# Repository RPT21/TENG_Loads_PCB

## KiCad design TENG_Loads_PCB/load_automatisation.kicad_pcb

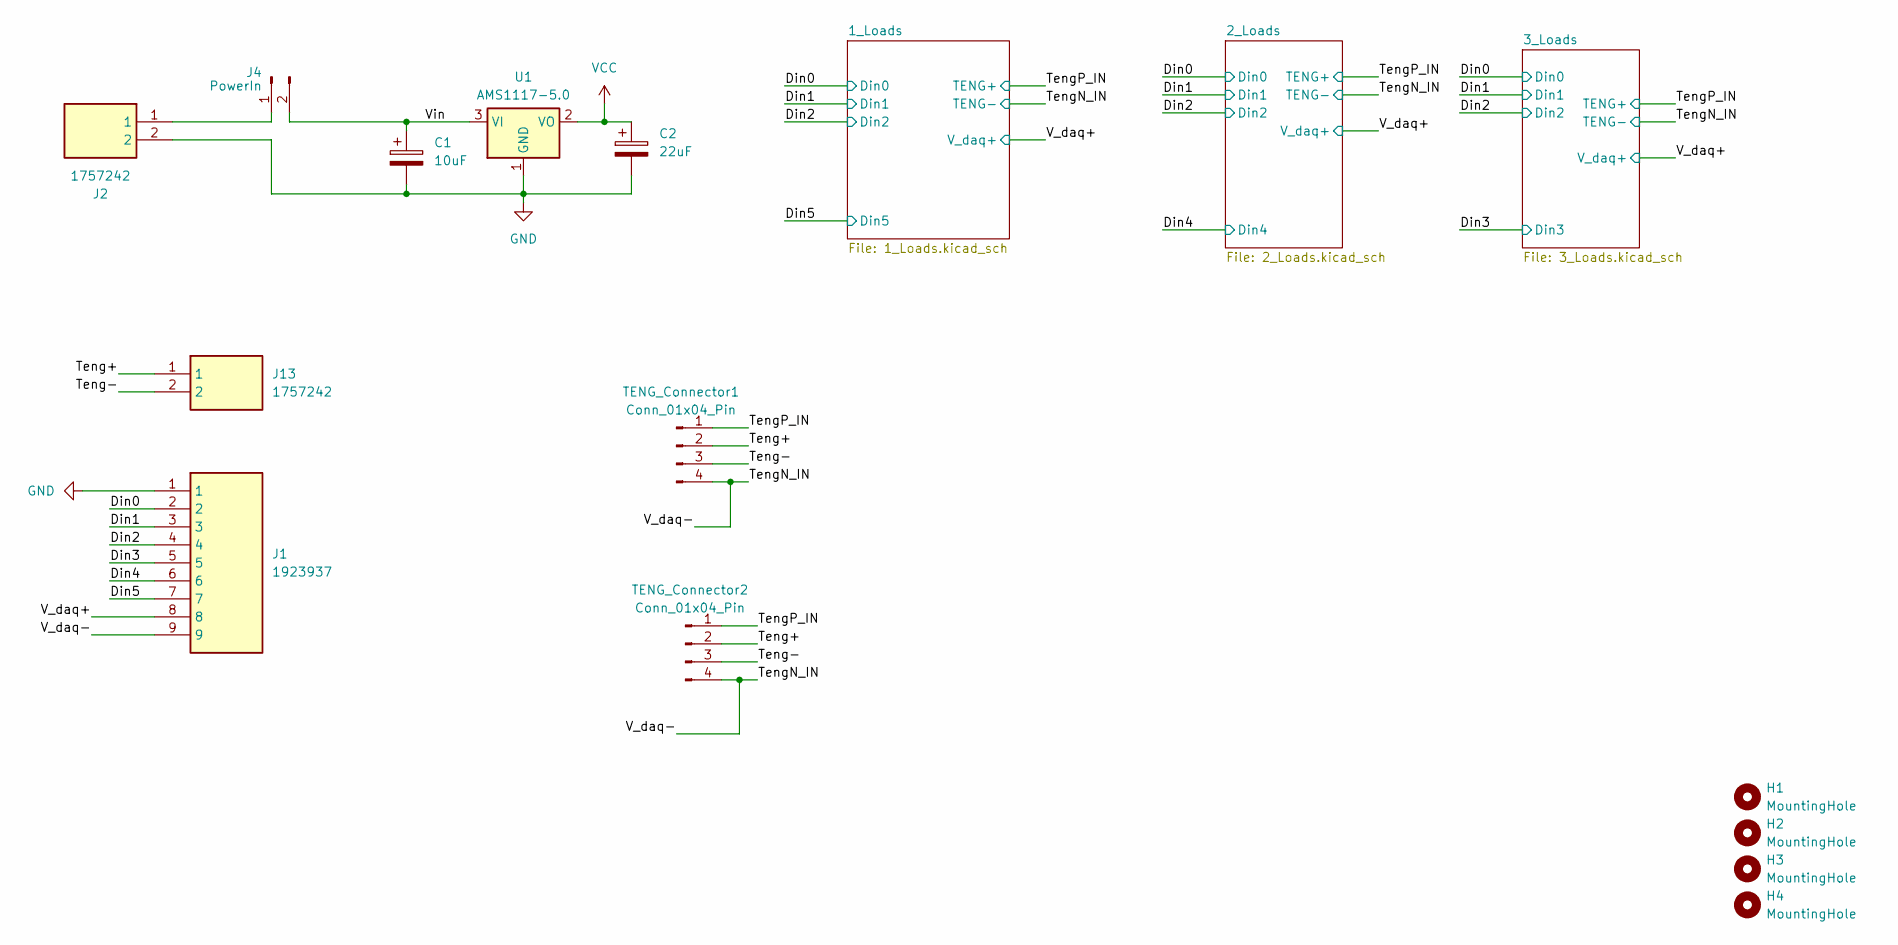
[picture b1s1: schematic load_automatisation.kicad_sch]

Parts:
C1: 10uF; CP_Radial_D8.0mm_P3.80mm
C2: 22uF; CP_Radial_D8.0mm_P3.80mm
H1, H2, H3, H4: MountingHole; MountingHole_5.3mm_M5
J1: 1923937; Mouser Part Number 651-1923937
J2, J13: 1757242; Manufacturer_Part_Number 1757242; Mouser Part Number 651-1757242
J4: PowerIn; PinHeader_1x02_P2.54mm_Vertical
TENG_Connector1, TENG_Connector2: Conn_01x04_Pin; PinHeader_1x04_P2.54mm_Vertical
U1: AMS1117-5.0; SOT-223-3_TabPin2

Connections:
/Din0: J1.2; also elsewhere on the board
/Din1: J1.3; also elsewhere on the board
/Din2: J1.4; also elsewhere on the board
/Din3: J1.5; also elsewhere on the board
/Din4: J1.6; also elsewhere on the board
/Din5: J1.7; also elsewhere on the board
/Teng+: J13.1, TENG_Connector1.2, TENG_Connector2.2
/Teng-: J13.2, TENG_Connector1.3, TENG_Connector2.3
/TengN_IN: J1.9, TENG_Connector1.4, TENG_Connector2.4; also elsewhere on the board
/TengP_IN: TENG_Connector1.1, TENG_Connector2.1; also elsewhere on the board
/V_daq+: J1.8; also elsewhere on the board
/Vin: C1.1, J4.2, U1.3 (VI)
GND: C1.2, C2.2, J1.1, J2.2, U1.1 (GND); also elsewhere on the board
unnamed: J2.1, J4.1
VCC: C2.1, U1.2 (VO); also elsewhere on the board

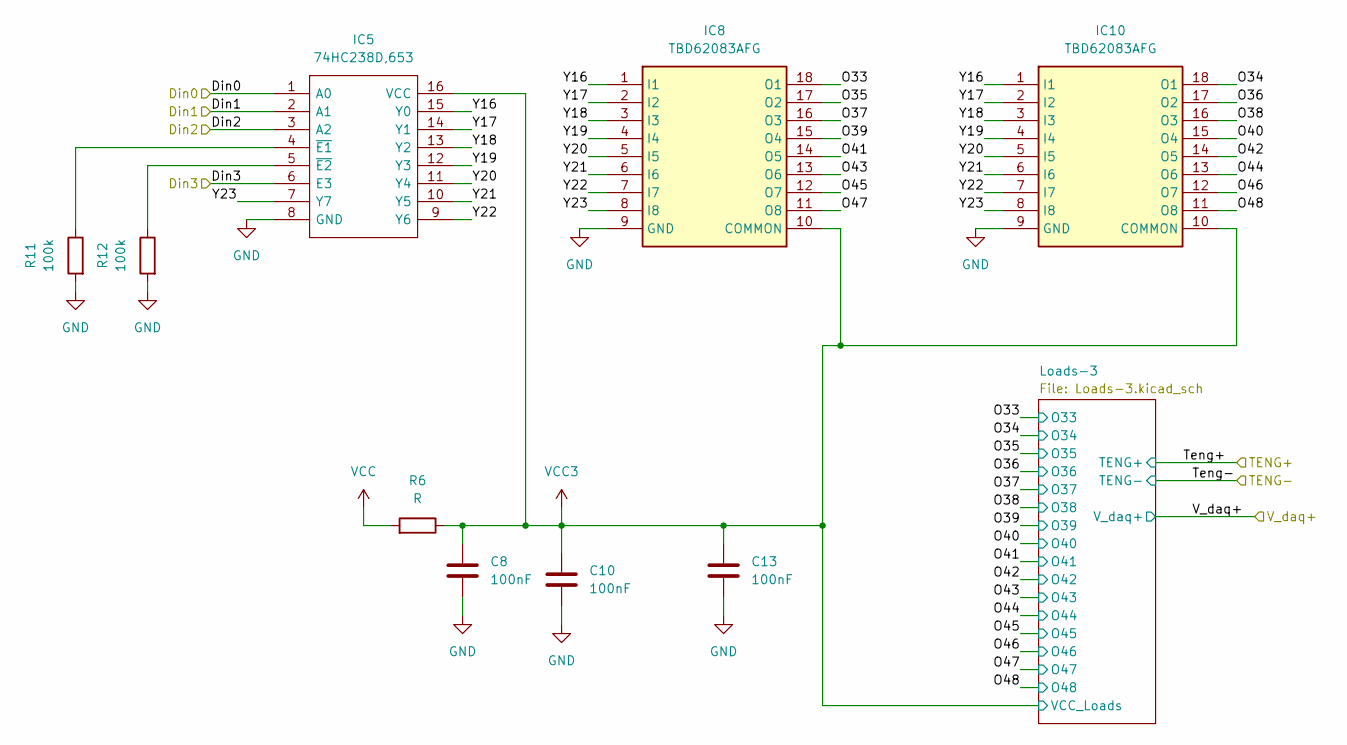
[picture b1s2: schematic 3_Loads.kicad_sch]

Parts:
C8, C10, C13: 100nF; C_0805_2012Metric
IC5: 74HC238D,653; 74HC238D653; Manufacturer_Part_Number 74HC238D,653; Mouser Part Number 771-74HC238D-T
IC8, IC10: TBD62083AFG; SOIC127P1030X245-18N; Manufacturer_Part_Number TD62083AFGNEL; Mouser Part Number N/A
R6: R; R_0805_2012Metric
R11, R12: 100k; R_0805_2012Metric

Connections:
/3_Loads/O33: IC8.18 (O1); also elsewhere on the board
/3_Loads/O34: IC10.18 (O1); also elsewhere on the board
/3_Loads/O35: IC8.17 (O2); also elsewhere on the board
/3_Loads/O36: IC10.17 (O2); also elsewhere on the board
/3_Loads/O37: IC8.16 (O3); also elsewhere on the board
/3_Loads/O38: IC10.16 (O3); also elsewhere on the board
/3_Loads/O39: IC8.15 (O4); also elsewhere on the board
/3_Loads/O40: IC10.15 (O4); also elsewhere on the board
/3_Loads/O41: IC8.14 (O5); also elsewhere on the board
/3_Loads/O42: IC10.14 (O5); also elsewhere on the board
/3_Loads/O43: IC8.13 (O6); also elsewhere on the board
/3_Loads/O44: IC10.13 (O6); also elsewhere on the board
/3_Loads/O45: IC8.12 (O7); also elsewhere on the board
/3_Loads/O46: IC10.12 (O7); also elsewhere on the board
/3_Loads/O47: IC8.11 (O8); also elsewhere on the board
/3_Loads/O48: IC10.11 (O8); also elsewhere on the board
/3_Loads/Y16: IC5.15 (Y0), IC8.1 (I1), IC10.1 (I1)
/3_Loads/Y17: IC5.14 (Y1), IC8.2 (I2), IC10.2 (I2)
/3_Loads/Y18: IC5.13 (Y2), IC8.3 (I3), IC10.3 (I3)
/3_Loads/Y19: IC5.12 (Y3), IC8.4 (I4), IC10.4 (I4)
/3_Loads/Y20: IC5.11 (Y4), IC8.5 (I5), IC10.5 (I5)
/3_Loads/Y21: IC5.10 (Y5), IC8.6 (I6), IC10.6 (I6)
/3_Loads/Y22: IC5.9 (Y6), IC8.7 (I7), IC10.7 (I7)
/3_Loads/Y23: IC5.7 (Y7), IC8.8 (I8), IC10.8 (I8)
/Din0: IC5.1 (A0); also elsewhere on the board
/Din1: IC5.2 (A1); also elsewhere on the board
/Din2: IC5.3 (A2); also elsewhere on the board
/Din3: IC5.6 (E3); also elsewhere on the board
GND: C8.2, C10.2, C13.2, IC5.8 (GND), IC8.9 (GND), IC10.9 (GND), R11.2, R12.2; also elsewhere on the board
unnamed: IC5.4 (~E1), R11.1
unnamed: IC5.5 (~E2), R12.1
VCC: R6.2; also elsewhere on the board
VCC3: C8.1, C10.1, C13.1, IC5.16 (VCC), IC8.10 (COMMON), IC10.10 (COMMON), R6.1; also elsewhere on the board

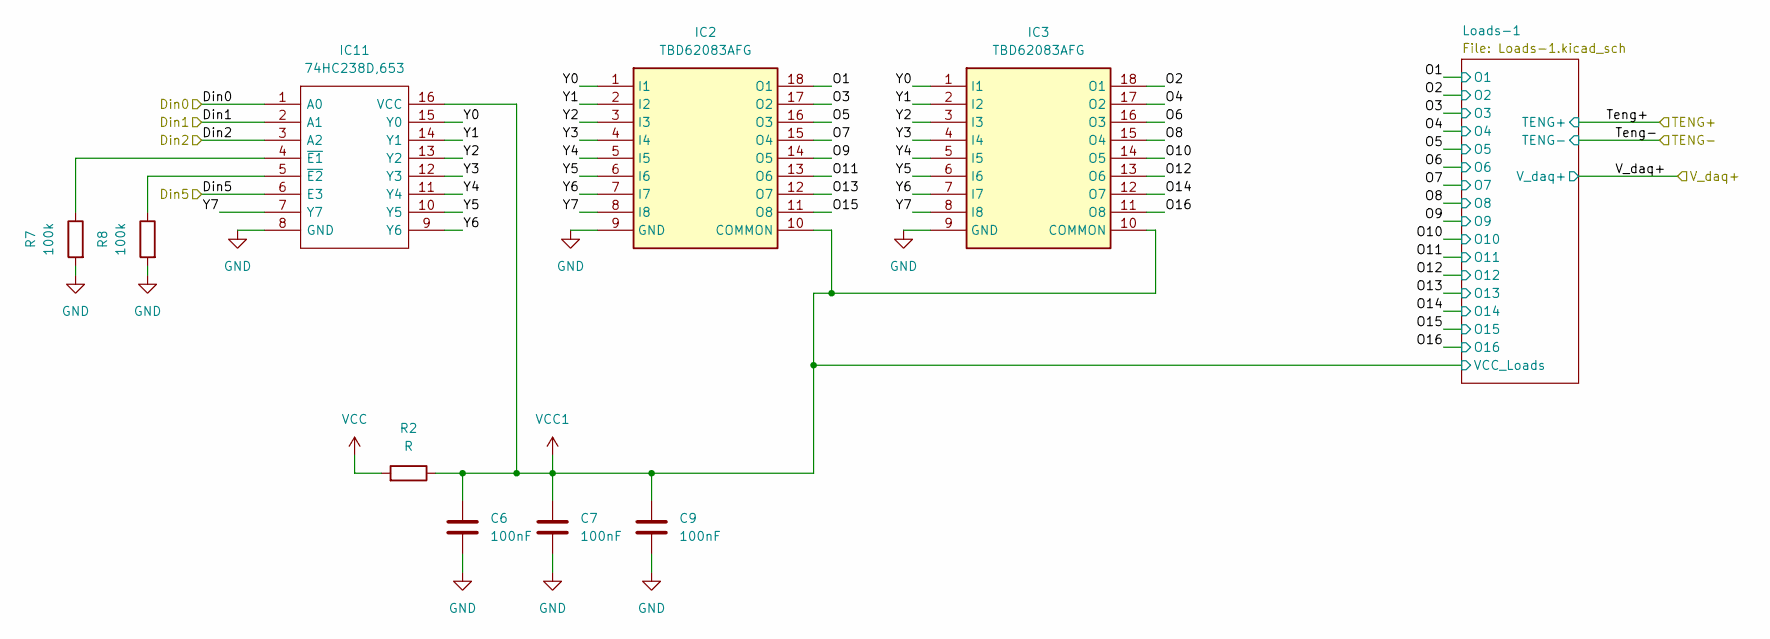
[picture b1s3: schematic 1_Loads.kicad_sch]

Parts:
C6, C7, C9: 100nF; C_0805_2012Metric
IC2, IC3: TBD62083AFG; SOIC127P1030X245-18N; Manufacturer_Part_Number TD62083AFGNEL; Mouser Part Number N/A
IC11: 74HC238D,653; 74HC238D653; Manufacturer_Part_Number 74HC238D,653; Mouser Part Number 771-74HC238D-T
R2: R; R_0805_2012Metric
R7, R8: 100k; R_0805_2012Metric

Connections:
/1_Loads/O1: IC2.18 (O1); also elsewhere on the board
/1_Loads/O2: IC3.18 (O1); also elsewhere on the board
/1_Loads/O3: IC2.17 (O2); also elsewhere on the board
/1_Loads/O4: IC3.17 (O2); also elsewhere on the board
/1_Loads/O5: IC2.16 (O3); also elsewhere on the board
/1_Loads/O6: IC3.16 (O3); also elsewhere on the board
/1_Loads/O7: IC2.15 (O4); also elsewhere on the board
/1_Loads/O8: IC3.15 (O4); also elsewhere on the board
/1_Loads/O9: IC2.14 (O5); also elsewhere on the board
/1_Loads/O10: IC3.14 (O5); also elsewhere on the board
/1_Loads/O11: IC2.13 (O6); also elsewhere on the board
/1_Loads/O12: IC3.13 (O6); also elsewhere on the board
/1_Loads/O13: IC2.12 (O7); also elsewhere on the board
/1_Loads/O14: IC3.12 (O7); also elsewhere on the board
/1_Loads/O15: IC2.11 (O8); also elsewhere on the board
/1_Loads/O16: IC3.11 (O8); also elsewhere on the board
/1_Loads/Y0: IC2.1 (I1), IC3.1 (I1), IC11.15 (Y0)
/1_Loads/Y1: IC2.2 (I2), IC3.2 (I2), IC11.14 (Y1)
/1_Loads/Y2: IC2.3 (I3), IC3.3 (I3), IC11.13 (Y2)
/1_Loads/Y3: IC2.4 (I4), IC3.4 (I4), IC11.12 (Y3)
/1_Loads/Y4: IC2.5 (I5), IC3.5 (I5), IC11.11 (Y4)
/1_Loads/Y5: IC2.6 (I6), IC3.6 (I6), IC11.10 (Y5)
/1_Loads/Y6: IC2.7 (I7), IC3.7 (I7), IC11.9 (Y6)
/1_Loads/Y7: IC2.8 (I8), IC3.8 (I8), IC11.7 (Y7)
/Din0: IC11.1 (A0); also elsewhere on the board
/Din1: IC11.2 (A1); also elsewhere on the board
/Din2: IC11.3 (A2); also elsewhere on the board
/Din5: IC11.6 (E3); also elsewhere on the board
GND: C6.2, C7.2, C9.2, IC2.9 (GND), IC3.9 (GND), IC11.8 (GND), R7.2, R8.2; also elsewhere on the board
unnamed: IC11.4 (~E1), R7.1
unnamed: IC11.5 (~E2), R8.1
VCC: R2.2; also elsewhere on the board
VCC1: C6.1, C7.1, C9.1, IC2.10 (COMMON), IC3.10 (COMMON), IC11.16 (VCC), R2.1; also elsewhere on the board

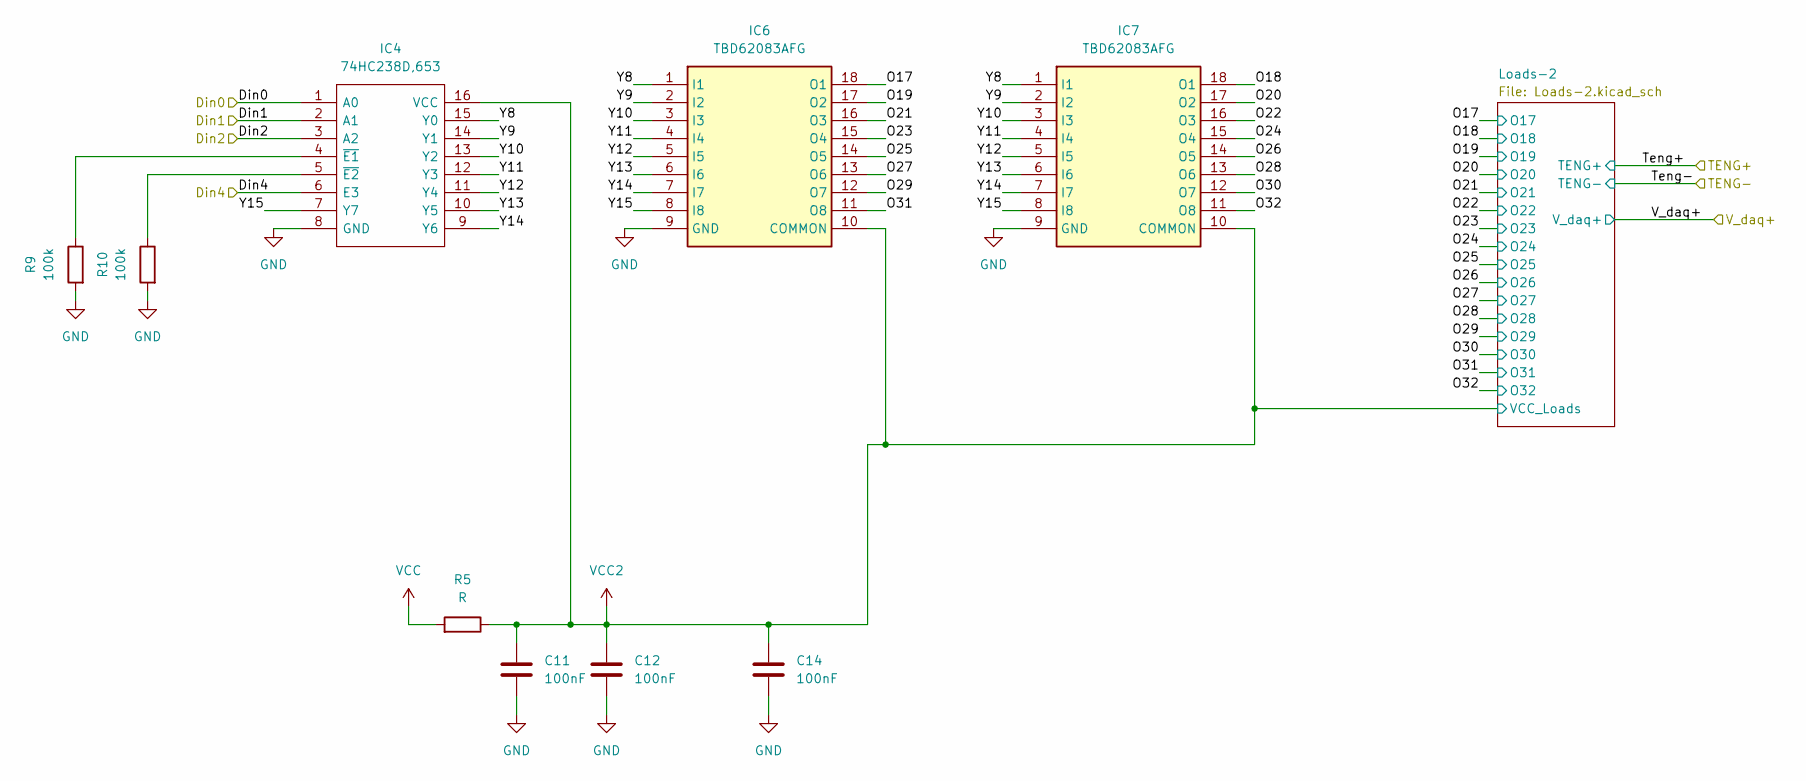
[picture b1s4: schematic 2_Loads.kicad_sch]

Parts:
C11, C12, C14: 100nF; C_0805_2012Metric
IC4: 74HC238D,653; 74HC238D653; Manufacturer_Part_Number 74HC238D,653; Mouser Part Number 771-74HC238D-T
IC6, IC7: TBD62083AFG; SOIC127P1030X245-18N; Manufacturer_Part_Number TD62083AFGNEL; Mouser Part Number N/A
R5: R; R_0805_2012Metric
R9, R10: 100k; R_0805_2012Metric

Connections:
/2_Loads/O17: IC6.18 (O1); also elsewhere on the board
/2_Loads/O18: IC7.18 (O1); also elsewhere on the board
/2_Loads/O19: IC6.17 (O2); also elsewhere on the board
/2_Loads/O20: IC7.17 (O2); also elsewhere on the board
/2_Loads/O21: IC6.16 (O3); also elsewhere on the board
/2_Loads/O22: IC7.16 (O3); also elsewhere on the board
/2_Loads/O23: IC6.15 (O4); also elsewhere on the board
/2_Loads/O24: IC7.15 (O4); also elsewhere on the board
/2_Loads/O25: IC6.14 (O5); also elsewhere on the board
/2_Loads/O26: IC7.14 (O5); also elsewhere on the board
/2_Loads/O27: IC6.13 (O6); also elsewhere on the board
/2_Loads/O28: IC7.13 (O6); also elsewhere on the board
/2_Loads/O29: IC6.12 (O7); also elsewhere on the board
/2_Loads/O30: IC7.12 (O7); also elsewhere on the board
/2_Loads/O31: IC6.11 (O8); also elsewhere on the board
/2_Loads/O32: IC7.11 (O8); also elsewhere on the board
/2_Loads/Y8: IC4.15 (Y0), IC6.1 (I1), IC7.1 (I1)
/2_Loads/Y9: IC4.14 (Y1), IC6.2 (I2), IC7.2 (I2)
/2_Loads/Y10: IC4.13 (Y2), IC6.3 (I3), IC7.3 (I3)
/2_Loads/Y11: IC4.12 (Y3), IC6.4 (I4), IC7.4 (I4)
/2_Loads/Y12: IC4.11 (Y4), IC6.5 (I5), IC7.5 (I5)
/2_Loads/Y13: IC4.10 (Y5), IC6.6 (I6), IC7.6 (I6)
/2_Loads/Y14: IC4.9 (Y6), IC6.7 (I7), IC7.7 (I7)
/2_Loads/Y15: IC4.7 (Y7), IC6.8 (I8), IC7.8 (I8)
/Din0: IC4.1 (A0); also elsewhere on the board
/Din1: IC4.2 (A1); also elsewhere on the board
/Din2: IC4.3 (A2); also elsewhere on the board
/Din4: IC4.6 (E3); also elsewhere on the board
GND: C11.2, C12.2, C14.2, IC4.8 (GND), IC6.9 (GND), IC7.9 (GND), R9.2, R10.2; also elsewhere on the board
unnamed: IC4.4 (~E1), R9.1
unnamed: IC4.5 (~E2), R10.1
VCC: R5.2; also elsewhere on the board
VCC2: C11.1, C12.1, C14.1, IC4.16 (VCC), IC6.10 (COMMON), IC7.10 (COMMON), R5.1; also elsewhere on the board

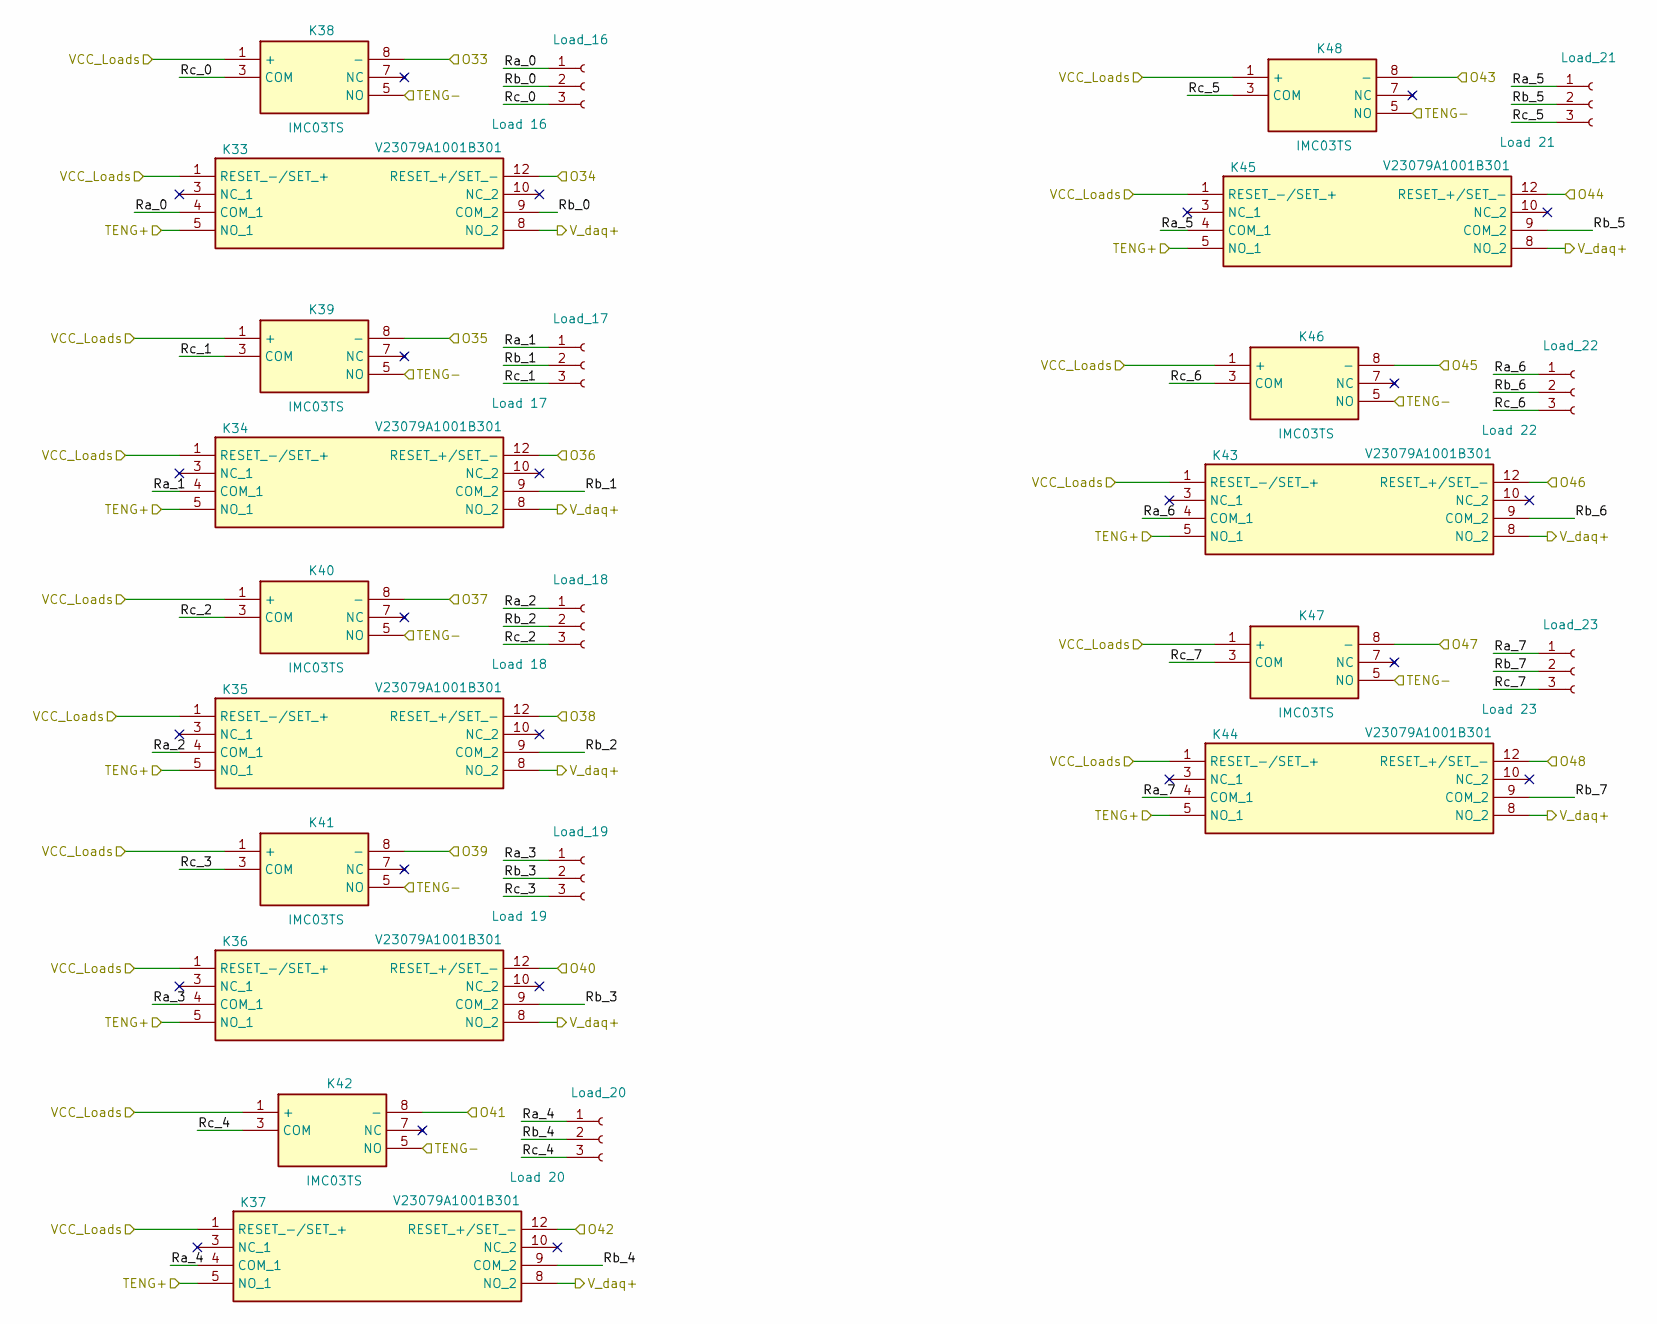
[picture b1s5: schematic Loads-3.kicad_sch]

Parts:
K33, K34, K35, K36, K37, K43, K44, K45: V23079A1001B301; Manufacturer_Part_Number V23079C1103B301; Mouser Part Number 655-V23079C1103B301
K38, K39, K40, K41, K42, K46, K47, K48: IMC03TS; Manufacturer_Part_Number IMC03TS; Mouser Part Number 655-IMC03TS
Load_16: Load 16; PinHeader_1x03_P2.54mm_Vertical
Load_17: Load 17; PinHeader_1x03_P2.54mm_Vertical
Load_18: Load 18; PinHeader_1x03_P2.54mm_Vertical
Load_19: Load 19; PinHeader_1x03_P2.54mm_Vertical
Load_20: Load 20; PinHeader_1x03_P2.54mm_Vertical
Load_21: Load 21; PinHeader_1x03_P2.54mm_Vertical
Load_22: Load 22; PinHeader_1x03_P2.54mm_Vertical
Load_23: Load 23; PinHeader_1x03_P2.54mm_Vertical

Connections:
/3_Loads/Loads-3/Ra_0: K33.4 (COM_1), Load_16.1
/3_Loads/Loads-3/Ra_1: K34.4 (COM_1), Load_17.1
/3_Loads/Loads-3/Ra_2: K35.4 (COM_1), Load_18.1
/3_Loads/Loads-3/Ra_3: K36.4 (COM_1), Load_19.1
/3_Loads/Loads-3/Ra_4: K37.4 (COM_1), Load_20.1
/3_Loads/Loads-3/Ra_5: K45.4 (COM_1), Load_21.1
/3_Loads/Loads-3/Ra_6: K43.4 (COM_1), Load_22.1
/3_Loads/Loads-3/Ra_7: K44.4 (COM_1), Load_23.1
/3_Loads/Loads-3/Rb_0: K33.9 (COM_2), Load_16.2
/3_Loads/Loads-3/Rb_1: K34.9 (COM_2), Load_17.2
/3_Loads/Loads-3/Rb_2: K35.9 (COM_2), Load_18.2
/3_Loads/Loads-3/Rb_3: K36.9 (COM_2), Load_19.2
/3_Loads/Loads-3/Rb_4: K37.9 (COM_2), Load_20.2
/3_Loads/Loads-3/Rb_5: K45.9 (COM_2), Load_21.2
/3_Loads/Loads-3/Rb_6: K43.9 (COM_2), Load_22.2
/3_Loads/Loads-3/Rb_7: K44.9 (COM_2), Load_23.2
/3_Loads/Loads-3/Rc_0: K38.3 (COM), Load_16.3
/3_Loads/Loads-3/Rc_1: K39.3 (COM), Load_17.3
/3_Loads/Loads-3/Rc_2: K40.3 (COM), Load_18.3
/3_Loads/Loads-3/Rc_3: K41.3 (COM), Load_19.3
/3_Loads/Loads-3/Rc_4: K42.3 (COM), Load_20.3
/3_Loads/Loads-3/Rc_5: K48.3 (COM), Load_21.3
/3_Loads/Loads-3/Rc_6: K46.3 (COM), Load_22.3
/3_Loads/Loads-3/Rc_7: K47.3 (COM), Load_23.3
/3_Loads/O33: K38.8 (-); also elsewhere on the board
/3_Loads/O34: K33.12 (RESET_+/SET_-); also elsewhere on the board
/3_Loads/O35: K39.8 (-); also elsewhere on the board
/3_Loads/O36: K34.12 (RESET_+/SET_-); also elsewhere on the board
/3_Loads/O37: K40.8 (-); also elsewhere on the board
/3_Loads/O38: K35.12 (RESET_+/SET_-); also elsewhere on the board
/3_Loads/O39: K41.8 (-); also elsewhere on the board
/3_Loads/O40: K36.12 (RESET_+/SET_-); also elsewhere on the board
/3_Loads/O41: K42.8 (-); also elsewhere on the board
/3_Loads/O42: K37.12 (RESET_+/SET_-); also elsewhere on the board
/3_Loads/O43: K48.8 (-); also elsewhere on the board
/3_Loads/O44: K45.12 (RESET_+/SET_-); also elsewhere on the board
/3_Loads/O45: K46.8 (-); also elsewhere on the board
/3_Loads/O46: K43.12 (RESET_+/SET_-); also elsewhere on the board
/3_Loads/O47: K47.8 (-); also elsewhere on the board
/3_Loads/O48: K44.12 (RESET_+/SET_-); also elsewhere on the board
/TengN_IN: K38.5 (NO), K39.5 (NO), K40.5 (NO), K41.5 (NO), K42.5 (NO), K46.5 (NO), K47.5 (NO), K48.5 (NO); also elsewhere on the board
/TengP_IN: K33.5 (NO_1), K34.5 (NO_1), K35.5 (NO_1), K36.5 (NO_1), K37.5 (NO_1), K43.5 (NO_1), K44.5 (NO_1), K45.5 (NO_1); also elsewhere on the board
/V_daq+: K33.8 (NO_2), K34.8 (NO_2), K35.8 (NO_2), K36.8 (NO_2), K37.8 (NO_2), K43.8 (NO_2), K44.8 (NO_2), K45.8 (NO_2); also elsewhere on the board
VCC3: K33.1 (RESET_-/SET_+), K34.1 (RESET_-/SET_+), K35.1 (RESET_-/SET_+), K36.1 (RESET_-/SET_+), K37.1 (RESET_-/SET_+), K38.1 (+), K39.1 (+), K40.1 (+), K41.1 (+), K42.1 (+), K43.1 (RESET_-/SET_+), K44.1 (RESET_-/SET_+), K45.1 (RESET_-/SET_+), K46.1 (+), K47.1 (+), K48.1 (+); also elsewhere on the board

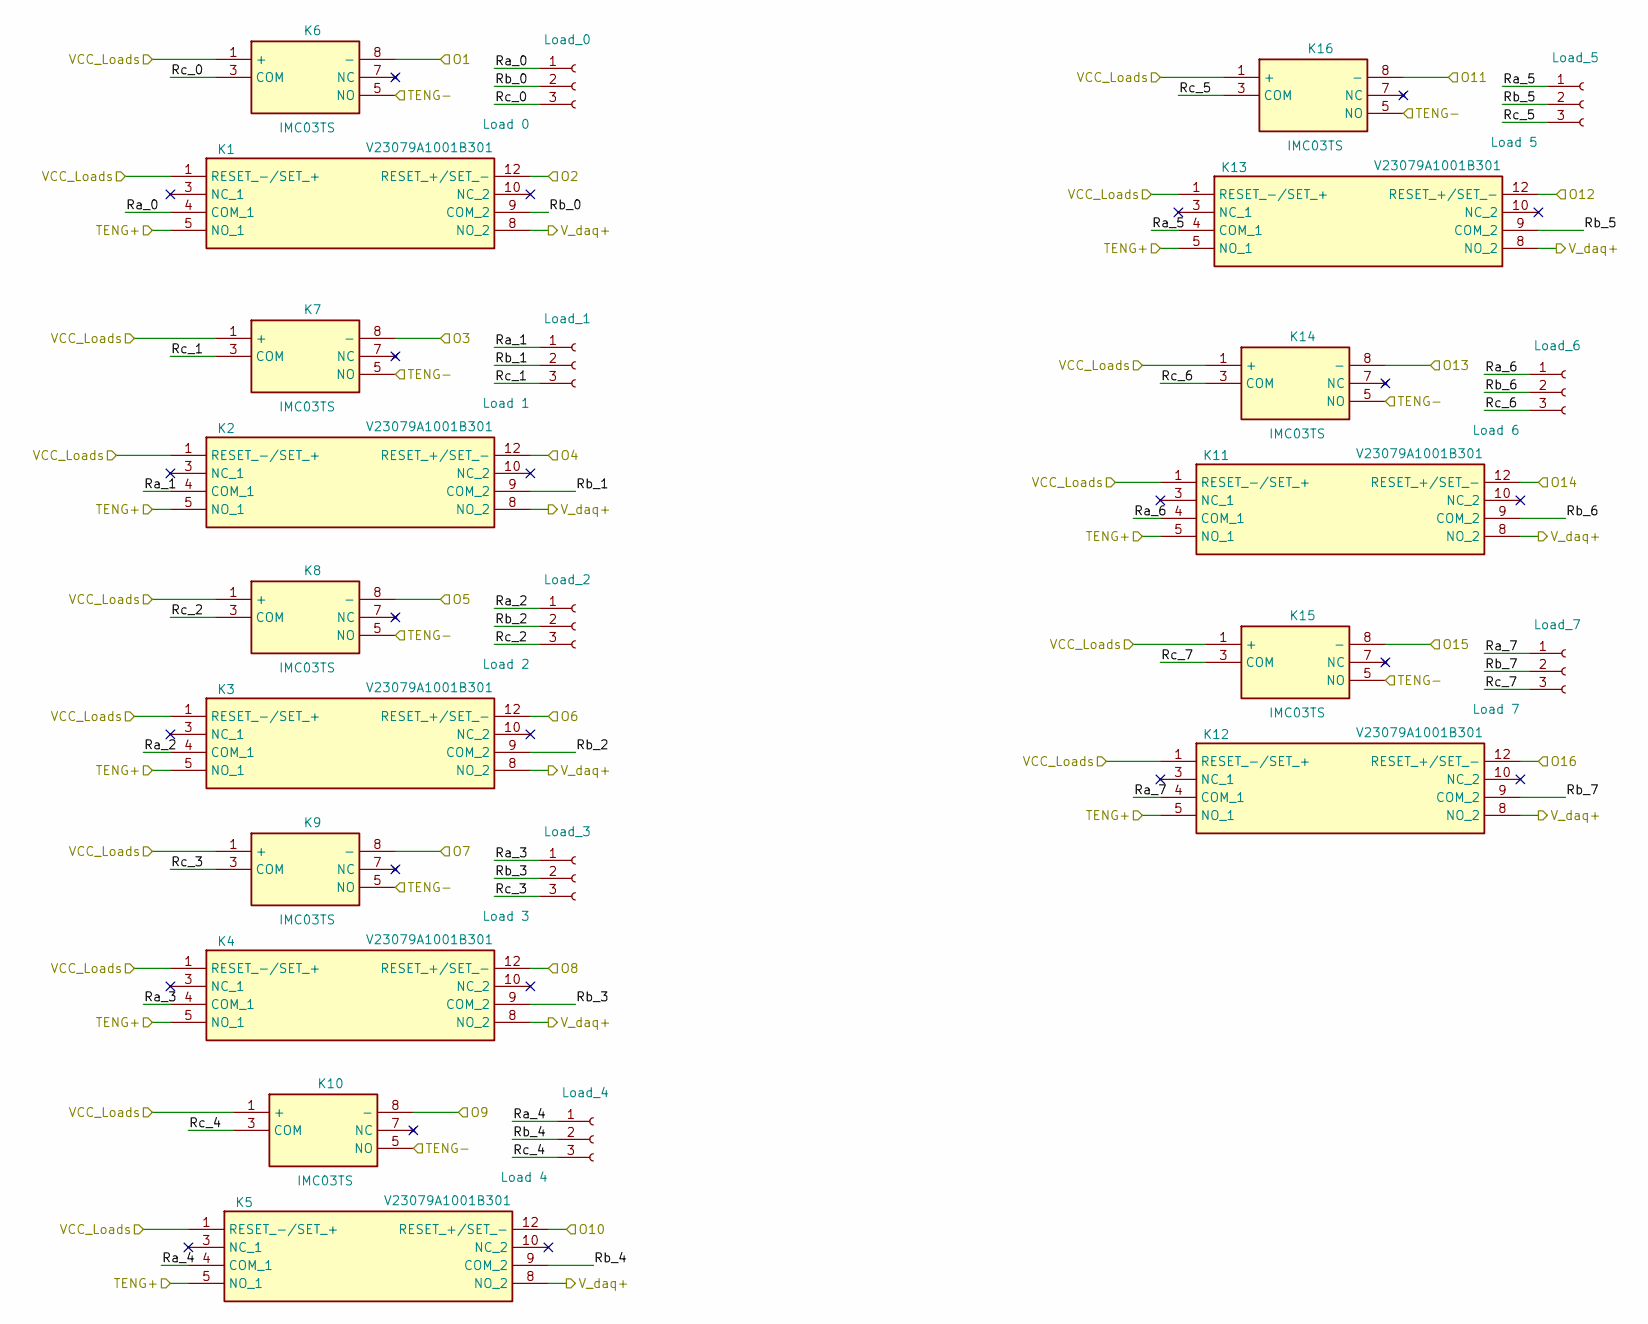
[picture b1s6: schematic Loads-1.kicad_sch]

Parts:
K1, K2, K3, K4, K5, K11, K12, K13: V23079A1001B301; Manufacturer_Part_Number V23079C1103B301; Mouser Part Number 655-V23079C1103B301
K6, K7, K8, K9, K10, K14, K15, K16: IMC03TS; Manufacturer_Part_Number IMC03TS; Mouser Part Number 655-IMC03TS
Load_0: Load 0; PinHeader_1x03_P2.54mm_Vertical
Load_1: Load 1; PinHeader_1x03_P2.54mm_Vertical
Load_2: Load 2; PinHeader_1x03_P2.54mm_Vertical
Load_3: Load 3; PinHeader_1x03_P2.54mm_Vertical
Load_4: Load 4; PinHeader_1x03_P2.54mm_Vertical
Load_5: Load 5; PinHeader_1x03_P2.54mm_Vertical
Load_6: Load 6; PinHeader_1x03_P2.54mm_Vertical
Load_7: Load 7; PinHeader_1x03_P2.54mm_Vertical

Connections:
/1_Loads/Loads-1/Ra_0: K1.4 (COM_1), Load_0.1
/1_Loads/Loads-1/Ra_1: K2.4 (COM_1), Load_1.1
/1_Loads/Loads-1/Ra_2: K3.4 (COM_1), Load_2.1
/1_Loads/Loads-1/Ra_3: K4.4 (COM_1), Load_3.1
/1_Loads/Loads-1/Ra_4: K5.4 (COM_1), Load_4.1
/1_Loads/Loads-1/Ra_5: K13.4 (COM_1), Load_5.1
/1_Loads/Loads-1/Ra_6: K11.4 (COM_1), Load_6.1
/1_Loads/Loads-1/Ra_7: K12.4 (COM_1), Load_7.1
/1_Loads/Loads-1/Rb_0: K1.9 (COM_2), Load_0.2
/1_Loads/Loads-1/Rb_1: K2.9 (COM_2), Load_1.2
/1_Loads/Loads-1/Rb_2: K3.9 (COM_2), Load_2.2
/1_Loads/Loads-1/Rb_3: K4.9 (COM_2), Load_3.2
/1_Loads/Loads-1/Rb_4: K5.9 (COM_2), Load_4.2
/1_Loads/Loads-1/Rb_5: K13.9 (COM_2), Load_5.2
/1_Loads/Loads-1/Rb_6: K11.9 (COM_2), Load_6.2
/1_Loads/Loads-1/Rb_7: K12.9 (COM_2), Load_7.2
/1_Loads/Loads-1/Rc_0: K6.3 (COM), Load_0.3
/1_Loads/Loads-1/Rc_1: K7.3 (COM), Load_1.3
/1_Loads/Loads-1/Rc_2: K8.3 (COM), Load_2.3
/1_Loads/Loads-1/Rc_3: K9.3 (COM), Load_3.3
/1_Loads/Loads-1/Rc_4: K10.3 (COM), Load_4.3
/1_Loads/Loads-1/Rc_5: K16.3 (COM), Load_5.3
/1_Loads/Loads-1/Rc_6: K14.3 (COM), Load_6.3
/1_Loads/Loads-1/Rc_7: K15.3 (COM), Load_7.3
/1_Loads/O1: K6.8 (-); also elsewhere on the board
/1_Loads/O2: K1.12 (RESET_+/SET_-); also elsewhere on the board
/1_Loads/O3: K7.8 (-); also elsewhere on the board
/1_Loads/O4: K2.12 (RESET_+/SET_-); also elsewhere on the board
/1_Loads/O5: K8.8 (-); also elsewhere on the board
/1_Loads/O6: K3.12 (RESET_+/SET_-); also elsewhere on the board
/1_Loads/O7: K9.8 (-); also elsewhere on the board
/1_Loads/O8: K4.12 (RESET_+/SET_-); also elsewhere on the board
/1_Loads/O9: K10.8 (-); also elsewhere on the board
/1_Loads/O10: K5.12 (RESET_+/SET_-); also elsewhere on the board
/1_Loads/O11: K16.8 (-); also elsewhere on the board
/1_Loads/O12: K13.12 (RESET_+/SET_-); also elsewhere on the board
/1_Loads/O13: K14.8 (-); also elsewhere on the board
/1_Loads/O14: K11.12 (RESET_+/SET_-); also elsewhere on the board
/1_Loads/O15: K15.8 (-); also elsewhere on the board
/1_Loads/O16: K12.12 (RESET_+/SET_-); also elsewhere on the board
/TengN_IN: K6.5 (NO), K7.5 (NO), K8.5 (NO), K9.5 (NO), K10.5 (NO), K14.5 (NO), K15.5 (NO), K16.5 (NO); also elsewhere on the board
/TengP_IN: K1.5 (NO_1), K2.5 (NO_1), K3.5 (NO_1), K4.5 (NO_1), K5.5 (NO_1), K11.5 (NO_1), K12.5 (NO_1), K13.5 (NO_1); also elsewhere on the board
/V_daq+: K1.8 (NO_2), K2.8 (NO_2), K3.8 (NO_2), K4.8 (NO_2), K5.8 (NO_2), K11.8 (NO_2), K12.8 (NO_2), K13.8 (NO_2); also elsewhere on the board
VCC1: K1.1 (RESET_-/SET_+), K2.1 (RESET_-/SET_+), K3.1 (RESET_-/SET_+), K4.1 (RESET_-/SET_+), K5.1 (RESET_-/SET_+), K6.1 (+), K7.1 (+), K8.1 (+), K9.1 (+), K10.1 (+), K11.1 (RESET_-/SET_+), K12.1 (RESET_-/SET_+), K13.1 (RESET_-/SET_+), K14.1 (+), K15.1 (+), K16.1 (+); also elsewhere on the board

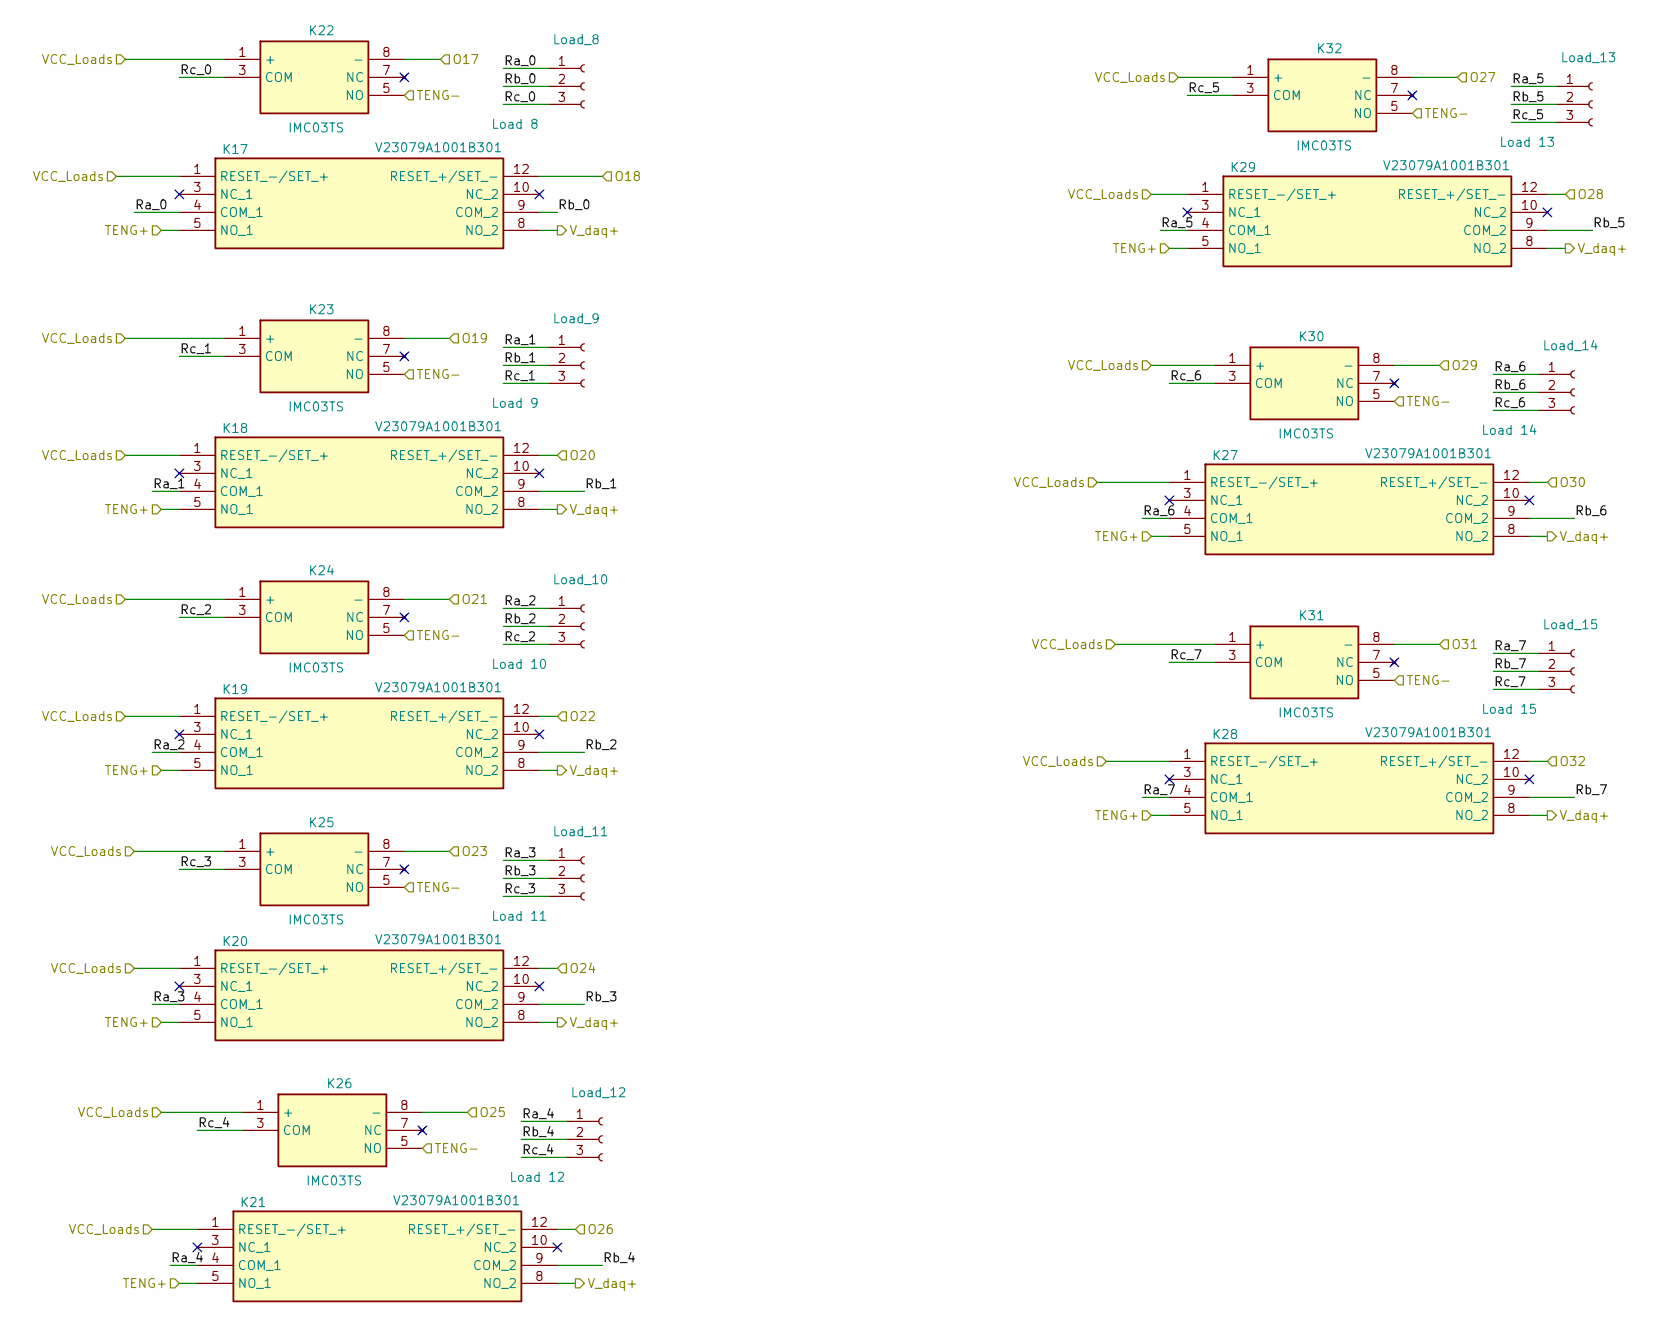
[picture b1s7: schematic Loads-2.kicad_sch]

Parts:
K17, K18, K19, K20, K21, K27, K28, K29: V23079A1001B301; Manufacturer_Part_Number V23079C1103B301; Mouser Part Number 655-V23079C1103B301
K22, K23, K24, K25, K26, K30, K31, K32: IMC03TS; Manufacturer_Part_Number IMC03TS; Mouser Part Number 655-IMC03TS
Load_8: Load 8; PinHeader_1x03_P2.54mm_Vertical
Load_9: Load 9; PinHeader_1x03_P2.54mm_Vertical
Load_10: Load 10; PinHeader_1x03_P2.54mm_Vertical
Load_11: Load 11; PinHeader_1x03_P2.54mm_Vertical
Load_12: Load 12; PinHeader_1x03_P2.54mm_Vertical
Load_13: Load 13; PinHeader_1x03_P2.54mm_Vertical
Load_14: Load 14; PinHeader_1x03_P2.54mm_Vertical
Load_15: Load 15; PinHeader_1x03_P2.54mm_Vertical

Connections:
/2_Loads/Loads-2/Ra_0: K17.4 (COM_1), Load_8.1
/2_Loads/Loads-2/Ra_1: K18.4 (COM_1), Load_9.1
/2_Loads/Loads-2/Ra_2: K19.4 (COM_1), Load_10.1
/2_Loads/Loads-2/Ra_3: K20.4 (COM_1), Load_11.1
/2_Loads/Loads-2/Ra_4: K21.4 (COM_1), Load_12.1
/2_Loads/Loads-2/Ra_5: K29.4 (COM_1), Load_13.1
/2_Loads/Loads-2/Ra_6: K27.4 (COM_1), Load_14.1
/2_Loads/Loads-2/Ra_7: K28.4 (COM_1), Load_15.1
/2_Loads/Loads-2/Rb_0: K17.9 (COM_2), Load_8.2
/2_Loads/Loads-2/Rb_1: K18.9 (COM_2), Load_9.2
/2_Loads/Loads-2/Rb_2: K19.9 (COM_2), Load_10.2
/2_Loads/Loads-2/Rb_3: K20.9 (COM_2), Load_11.2
/2_Loads/Loads-2/Rb_4: K21.9 (COM_2), Load_12.2
/2_Loads/Loads-2/Rb_5: K29.9 (COM_2), Load_13.2
/2_Loads/Loads-2/Rb_6: K27.9 (COM_2), Load_14.2
/2_Loads/Loads-2/Rb_7: K28.9 (COM_2), Load_15.2
/2_Loads/Loads-2/Rc_0: K22.3 (COM), Load_8.3
/2_Loads/Loads-2/Rc_1: K23.3 (COM), Load_9.3
/2_Loads/Loads-2/Rc_2: K24.3 (COM), Load_10.3
/2_Loads/Loads-2/Rc_3: K25.3 (COM), Load_11.3
/2_Loads/Loads-2/Rc_4: K26.3 (COM), Load_12.3
/2_Loads/Loads-2/Rc_5: K32.3 (COM), Load_13.3
/2_Loads/Loads-2/Rc_6: K30.3 (COM), Load_14.3
/2_Loads/Loads-2/Rc_7: K31.3 (COM), Load_15.3
/2_Loads/O17: K22.8 (-); also elsewhere on the board
/2_Loads/O18: K17.12 (RESET_+/SET_-); also elsewhere on the board
/2_Loads/O19: K23.8 (-); also elsewhere on the board
/2_Loads/O20: K18.12 (RESET_+/SET_-); also elsewhere on the board
/2_Loads/O21: K24.8 (-); also elsewhere on the board
/2_Loads/O22: K19.12 (RESET_+/SET_-); also elsewhere on the board
/2_Loads/O23: K25.8 (-); also elsewhere on the board
/2_Loads/O24: K20.12 (RESET_+/SET_-); also elsewhere on the board
/2_Loads/O25: K26.8 (-); also elsewhere on the board
/2_Loads/O26: K21.12 (RESET_+/SET_-); also elsewhere on the board
/2_Loads/O27: K32.8 (-); also elsewhere on the board
/2_Loads/O28: K29.12 (RESET_+/SET_-); also elsewhere on the board
/2_Loads/O29: K30.8 (-); also elsewhere on the board
/2_Loads/O30: K27.12 (RESET_+/SET_-); also elsewhere on the board
/2_Loads/O31: K31.8 (-); also elsewhere on the board
/2_Loads/O32: K28.12 (RESET_+/SET_-); also elsewhere on the board
/TengN_IN: K22.5 (NO), K23.5 (NO), K24.5 (NO), K25.5 (NO), K26.5 (NO), K30.5 (NO), K31.5 (NO), K32.5 (NO); also elsewhere on the board
/TengP_IN: K17.5 (NO_1), K18.5 (NO_1), K19.5 (NO_1), K20.5 (NO_1), K21.5 (NO_1), K27.5 (NO_1), K28.5 (NO_1), K29.5 (NO_1); also elsewhere on the board
/V_daq+: K17.8 (NO_2), K18.8 (NO_2), K19.8 (NO_2), K20.8 (NO_2), K21.8 (NO_2), K27.8 (NO_2), K28.8 (NO_2), K29.8 (NO_2); also elsewhere on the board
VCC2: K17.1 (RESET_-/SET_+), K18.1 (RESET_-/SET_+), K19.1 (RESET_-/SET_+), K20.1 (RESET_-/SET_+), K21.1 (RESET_-/SET_+), K22.1 (+), K23.1 (+), K24.1 (+), K25.1 (+), K26.1 (+), K27.1 (RESET_-/SET_+), K28.1 (RESET_-/SET_+), K29.1 (RESET_-/SET_+), K30.1 (+), K31.1 (+), K32.1 (+); also elsewhere on the board
